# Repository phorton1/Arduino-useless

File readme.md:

# Useless Box

- Servo Arm
- Servo Lid
- 4 x Servo Wheels
- LEDs
- IR Sensors
- Compass (for returning after spin move)

## Session Lifecycle

The box initiates a session with someone the first time the switch is thrown.
A session times out after a period (i.e. 1 minute) of activity.

# types of behaviors

- sneaky fast = no lid, fast move to turn off
- slow = open lid, slowly turn off, slowly reverses
- almost, then = move till almost off, wait, then turn off, fast or slow retreat
- jitter = up to including almost position
- lid jitter = down to and including slapping
- waiting = until hand moves away, and/or some amount of time
- moving = left, right, turn left, turn right, rotate, counter-rotate, find front (with compass)
- front lights are generally white on and black off
- inside lights can be synchronized to each move thing and or flash independently
- ir stuff: besides moves, open door, watch, move arm into position
- lock arm

- outside lights can be indicators, i.e. for ir sensors

// OVERIDING DESIGN CONSIDERATION
//
// Calling neoPixels.show() while servos are attached causes jitter in the servos.
//
// Therefor care must be taken to coordinate the movement of servos with pixel changes.
//
// In general we keep the servos detached when not in use.
// The only place that *might* be a problem is holding up a spring loaded lid.
//
// Jitter is unimportant in the wheels.

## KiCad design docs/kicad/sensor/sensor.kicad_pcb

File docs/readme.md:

# Useless Box

**Home** --
**[Electronics](electronics.md)** --
**[Wood](wood.md)** --
**[Top](top.md)** --
**[Bottom](bottom.md)** --
**[Software](software.md)**

For the fun of it, I mada a **Useless Box**.

**Insert YouTube Demo movie here**

All of the **fusion360 files** and the **STL** and **DXF** files exported from fusion, as well as
the **Prusa Slicer** and **Gcode** files and **Lightburn** projects I then used to print the
plastic parts and laser cut the wood can be found in the following subdirecties in the **docs** folder

- **fusion** - the fusion 360 design files
- **stl** - the STL files that I used to slice the plastic parts
- **dxf** - the DXF files that I used to laser cut the wood parts
- **prusa** - the Prusa slicer files and resultant gcode I used to print the plastic parts
- **lightburn** - the Lightburn projects I used to cut the wood.

## Design

I decided on the following basic set of requirements for my useless box

- random **behaviors** - it will be controlled by an arduino nano with various random behaviors
- **mobility** - it will have motors and semi-hidden wheels so it can spin, move left and right, etc
- **sensors** - it will have sensors, probably infrared, to detect when a human tries to touch it
- **leds** - it will have a string of WD2812b leds that will light up the interior for effect and probably some on the top to show the user
- **on-off switch** - it will have an on/off switch to the power supply
- **batteries** - it will use rechargable 18650 Lithium batteries, because I have a bunch of those, and pre-made plastic holders for them
- **nicely constructed** - it will look nice, like a bit of a wood working effort

I had recently upgraded my [**home built cnc machine**](https://github.com/phorton1/Arduino-esp32_cnc20mm) with a new 10W laser, and
had been having a lot of fun making wooden boxes with it, and this seemed like a perfect opportunity to combine that with
some electronics and programming to make something interesting.  I had a bunch of inexpensive **3/16" plywood** that I had
become proficient in cutting and glueing, so I decided the box would be made out of that.

I decided to use small MG90 Servos.  I tested them against a dual 3.7V (7.4V total) 18650 battery pair and, although they get hot
if left running continuously, for short bursts they work ok, and in my application they would not need to be kept running or
holding any positions against any serious forces.  The extra voltage (they are rated at 5V) resulted in extra torque so I felt
that I did not need the much larger kinds of servos that other similar box makers seemed to insist on using.

I also knew that I had bought a number of of "continuous" MG90 servos (by mistake) for an earlier project.  Those turned out to
be perfect for running the motors for the wheels.  I can easily control which way, as well as the speed, each wheel turns with a fair degree
of accuracy.

I decided I would 3D print wheels that made use of some 30mm rubber O-rings that I had.

I used one piece of **1/8" plywood** for the partition.

### Bill of Materials

- one SPDT blue switch and nut for the top
- one slider SPST switch for the power supply
- a 2 cell 18650 battery holder
- two 90 degree MG90 servos and screws
- four continuous MG90 servos and screws
- four 30x2mm rubber O-rings
- ws2812B LED strip
- two M2x12 screws for the back
- one M3x12 screw for the front
- four or five small screws to hold the main circuit board
- two four wired JST connectors for the sensors
- two two wired JST connectors, one for the power supply, and one for the switch
- two sensor cicruit boards, made below
- one main circuit board, made below
- 3D printed parts, made below
- laster cut wood parts, made below

## Please See

**Please see the following additional pages**

- **[Electronics](electronics.md)** - schematics and circuit boards for the box
- **[Wood](wood.md)** - assembling the wooden box
- **[Top](top.md)** - adding the LEDs, sensors, and switch to the top of the box
- **[Bottom](bottom.md)** - buildling the bottom of the box (Arduino, Batteries, Power Switch, Servos)
- **[Software](software.md)** - a description of the Arduino sketch for the box

## License

This program is free software: you can redistribute it and/or modify
it under the terms of the GNU General Public License Version 3 as published by
the Free Software Foundation.

This program is distributed in the hope that it will be useful,
but WITHOUT ANY WARRANTY; without even the implied warranty of
MERCHANTABILITY or FITNESS FOR A PARTICULAR PURPOSE.  See the
GNU General Public License for more details.

Please see [LICENSE.TXT](https://github.com/phorton1/Arduino-libraries-myIOT/blob/master/LICENSE.TXT) for more information.

**Next:** The [**Electronics**](electronics.md), schematics, and circuit boards used in the box ...

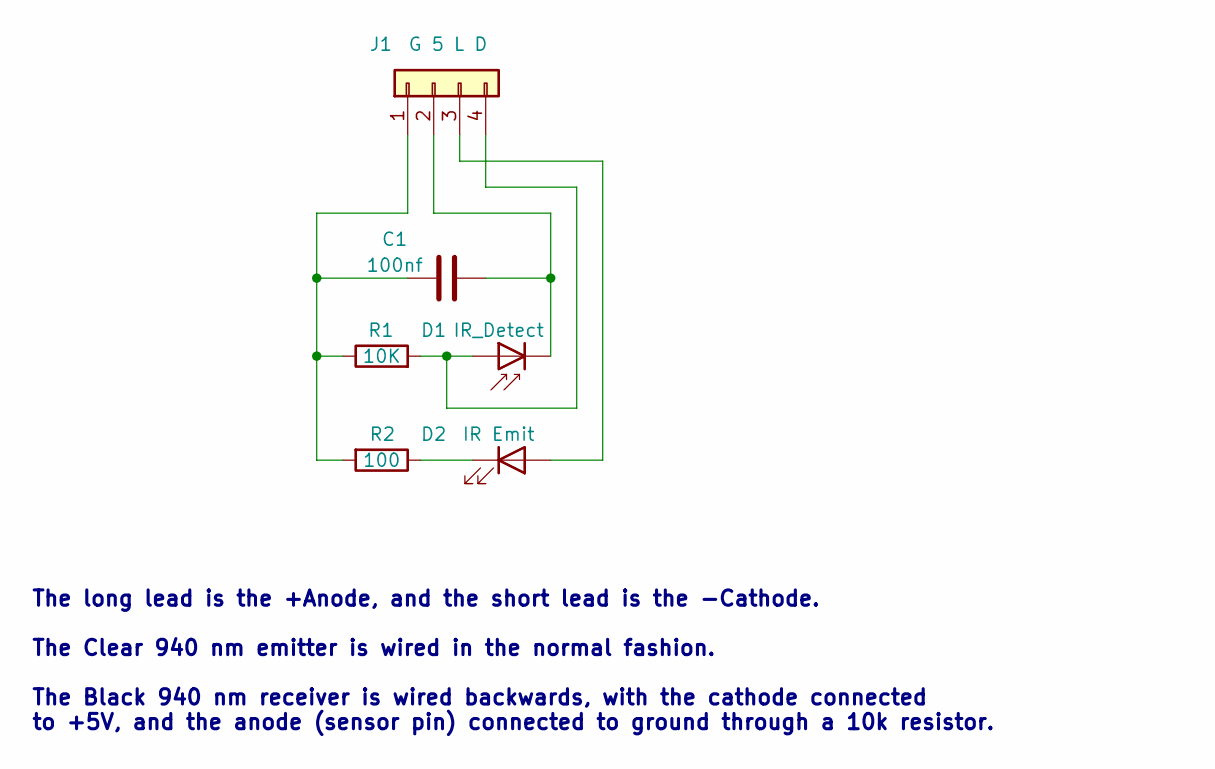
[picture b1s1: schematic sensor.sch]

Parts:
C1: 100nf; my2pin
D1: IR_Detect; my2pin
D2: IR Emit; my2pin
J1: G 5 L D; my4pin
R1: 10K; myResistor
R2: 100; myResistor

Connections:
+5V: C1.1, D1.1 (K), J1.2
GND: C1.2, J1.1, R1.1, R2.2
unnamed: D1.2 (A), J1.4, R1.2
unnamed: D2.1 (K), R2.1
unnamed: D2.2 (A), J1.3

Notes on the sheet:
The long lead is the +Anode, and the short lead is the -Cathode. The Clear 940 nm emitter is wired in the normal fashion. The Black 940 nm receiver is wired backwards, with the cathode connected to +5V, and the anode (sensor pin) connected to ground through a 10k resistor.

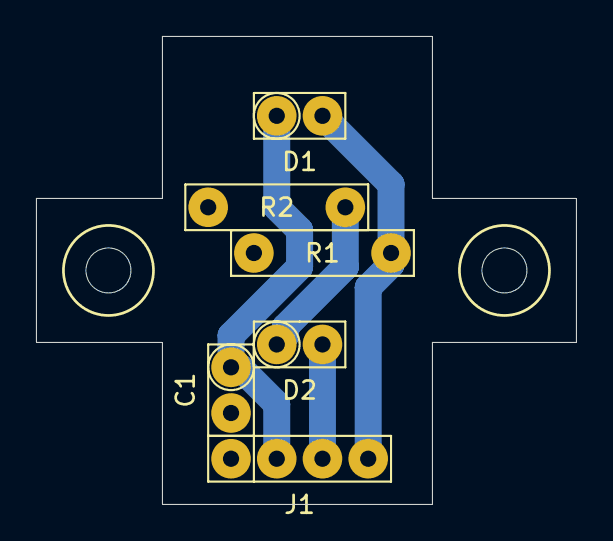
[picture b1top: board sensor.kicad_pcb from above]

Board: 2 copper layers, 30.0 x 26.0 mm, 6 parts (0 on the bottom side), 5 nets.

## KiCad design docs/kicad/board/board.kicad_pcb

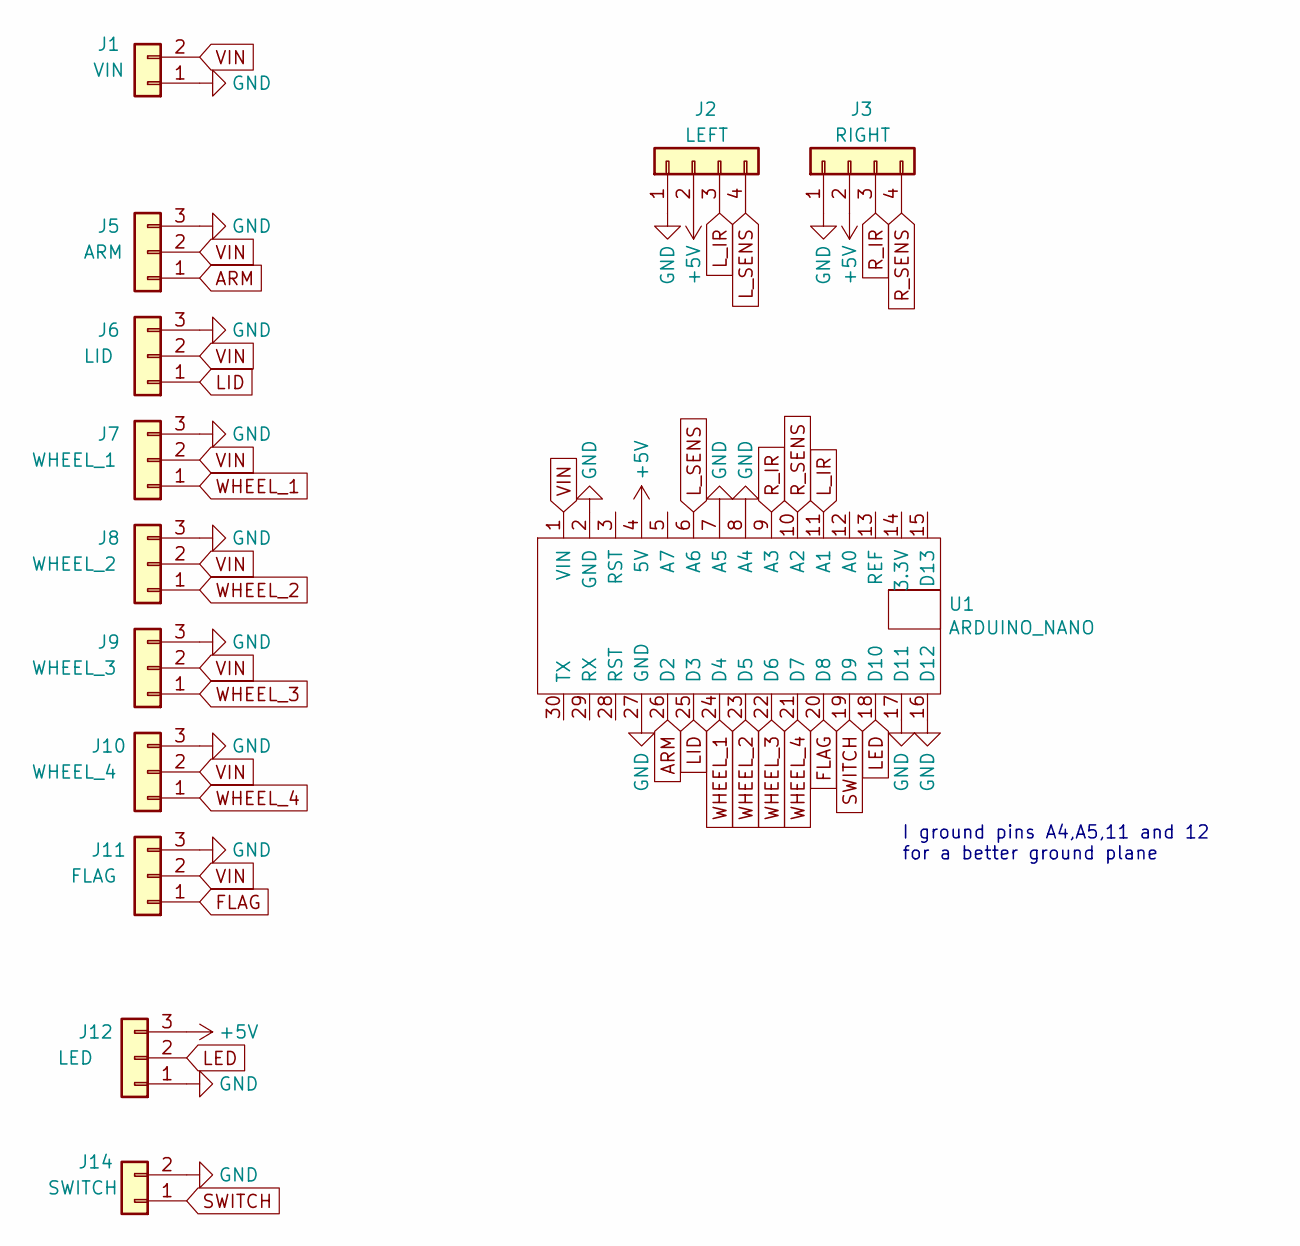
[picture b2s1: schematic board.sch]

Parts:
J1: VIN; myJSTx02
J2: LEFT; myJSTx04
J3: RIGHT; myJSTx04
J5: ARM; myPinHeader_1x03
J6: LID; myPinHeader_1x03
J7: WHEEL_1; myPinHeader_1x03
J8: WHEEL_2; myPinHeader_1x03
J9: WHEEL_3; myPinHeader_1x03
J10: WHEEL_4; myPinHeader_1x03
J11: FLAG; myPinHeader_1x03
J12: LED; myJSTx03
J14: SWITCH; myJSTx02
U1: ARDUINO_NANO; myArduinoNano

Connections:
+5V: J2.2, J3.2, J12.3, U1.4 (5V)
ARM: J5.1, U1.26 (D2)
FLAG: J11.1, U1.20 (D8)
GND: J1.1, J2.1, J3.1, J5.3, J6.3, J7.3, J8.3, J9.3, J10.3, J11.3, J12.1, J14.2, U1.2 (GND), U1.7 (A5), U1.8 (A4), U1.16 (D12), U1.17 (D11), U1.27 (GND)
LED: J12.2, U1.18 (D10)
LID: J6.1, U1.25 (D3)
L_IR: J2.3, U1.11 (A1)
L_SENS: J2.4, U1.6 (A6)
R_IR: J3.3, U1.9 (A3)
R_SENS: J3.4, U1.10 (A2)
SWITCH: J14.1, U1.19 (D9)
VIN: J1.2, J5.2, J6.2, J7.2, J8.2, J9.2, J10.2, J11.2, U1.1 (VIN)
WHEEL_1: J7.1, U1.24 (D4)
WHEEL_2: J8.1, U1.23 (D5)
WHEEL_3: J9.1, U1.22 (D6)
WHEEL_4: J10.1, U1.21 (D7)

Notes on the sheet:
I ground pins A4,A5,11 and 12 for a better ground plane

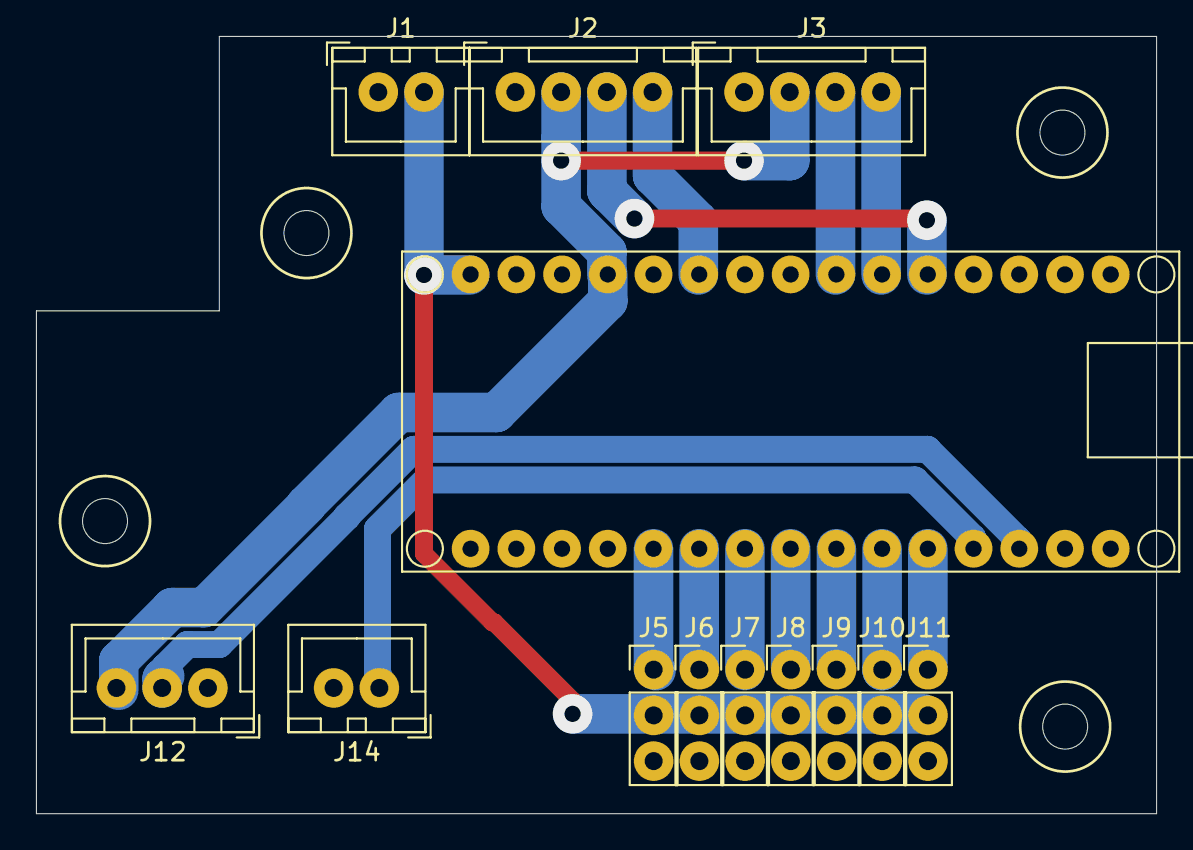
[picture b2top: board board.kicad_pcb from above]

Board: 2 copper layers, 62.2 x 43.2 mm, 13 parts (0 on the bottom side), 16 nets.

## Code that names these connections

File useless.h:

// useless.h

#pragma once

#include <Arduino.h>

#define PIN_ARM				2
#define PIN_LID		  		3
#define PIN_WHEEL_FL  		4
#define PIN_WHEEL_BL		5
#define PIN_WHEEL_BR		6
#define PIN_WHEEL_FR		7
#define PIN_UNUSED_SERVO	8
#define PIN_SWITCH			9
#define PIN_LED_STRIP		10
#define PIN_L_LED			A1	// jumper wire
#define PIN_L_SENSE			A6
#define PIN_R_LED			A3
#define PIN_R_SENSE			A2
#define PIN_SCL				A5
#define PIN_SDA				A4

#define SERVO_ARM			0
#define SERVO_LID		  	1
#define SERVO_WHEEL_FL  	2
#define SERVO_WHEEL_BL		3
#define SERVO_WHEEL_BR		4
#define SERVO_WHEEL_FR		5
#define NUM_SERVOS   		6

#define WITH_PIXELS			1
#define WITH_IR				1
	// These defines can be turned of for debugging if you think
	// the Neopixels or IR are not playing well with the servos
	// or each other.

#define TEST_MODE			0
	// TEST_MODE can be set to one to allow you control, and
	// verify the function and direction of the wheels via the
	// Serial monitor.
#define TEST_IR				0	// 500
	// if TEST_IR is not zero, this is the millisecond delay
	// for output the IR sensor state for debugging.


extern bool switch_state;

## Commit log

2022-09-25 initial build and test
2022-09-25 initial basic architecture
2022-09-25 early prototyping - moving towards varSpeedServo library
2022-09-26 basic acts and initial steps in place
2022-09-27 infrared in-between done
2022-09-27 basic wheel moves
2022-09-27 implemented "compass mode" and buttons for brightness and mode changes
2022-09-27 generalized randomization scheme, "fixed" homing, implemented first moves (and replaced servo cuz I had my hand on the box and broke the lid plastic gears)
2022-09-28 tune acts
2022-10-16 final version
2022-12-08 Built version 2 for Daniel
2022-12-30 WIP - useless box documentation
2023-01-01 initial documentation
2023-01-01 Added documentation content files
2023-01-01 got rid of old readme
2023-01-01 fixed typo
2023-01-13 created 3D rendering of PCB with my new kicad footprint files
2023-01-15 commit new board schematic using my new symbols and 3D footprints
2023-05-01 SIMPLIFY: got rid of buttons and compass, smaller PCB, all new outputs
2023-05-02 re-plot, build for NOAH
2023-05-02 BUILD FOR NOAH - tuning to specific IR's, servos, and arduinos
2023-05-02 more tuning. moved lights off to end of acts. STILL FREEZES SOMETIMES
2023-10-10 minor changes while cleaning up repositories
